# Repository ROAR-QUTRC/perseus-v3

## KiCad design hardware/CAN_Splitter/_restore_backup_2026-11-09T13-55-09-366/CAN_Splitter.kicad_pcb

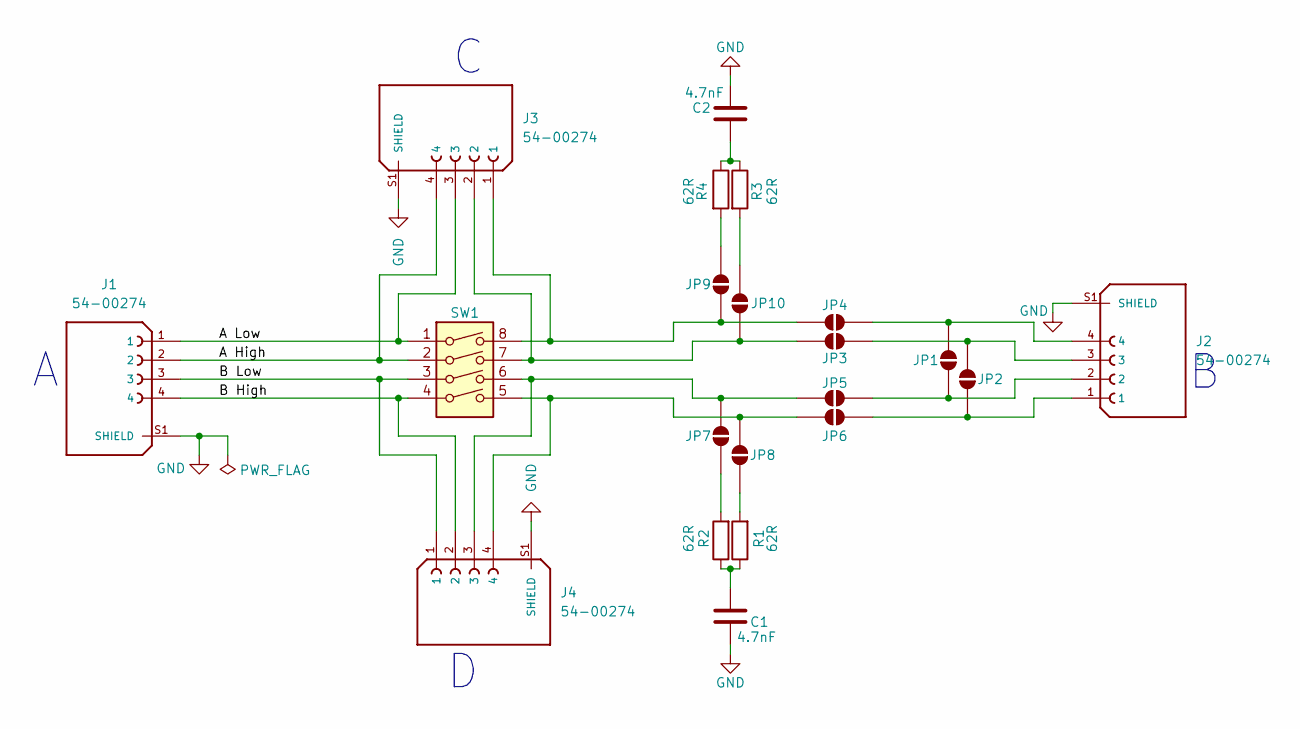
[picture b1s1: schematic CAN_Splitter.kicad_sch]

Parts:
C1, C2: 4.7nF; C_0603_1608Metric; digikey_part_num 1276-CL03B472KASVPNCCT-ND
J1, J2, J3, J4: 54-00274; TENSILITY_54-00274; MPN 54-00274; DigiKey_Part_Number 839-54-00274-ND
JP1, JP2, JP3, JP4, JP5, JP6, JP7, JP8, JP9, JP10: SolderJumper_2_Open; SolderJumper-2_P1.3mm_Open_RoundedPad1.0x1.5mm
R1, R2, R3, R4: 62R; C_0603_1608Metric; digikey_part_num RMCF0603FT62R0CT-ND
SW1: SW_DIP_x04; SW_DIP_SPSTx04_Slide_Copal_CHS-04A_W5.08mm_P1.27mm_JPin

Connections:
/A High: J1.2, J3.4, SW1.2
/A Low: J1.1, J3.3, SW1.1
/B High: J1.4, J4.2, SW1.4
/B Low: J1.3, J4.1, SW1.3
GND: C1.2, C2.2, J1.S1 (SHIELD), J1.S2 (SHIELD), J2.S1 (SHIELD), J2.S2 (SHIELD), J3.S1 (SHIELD), J3.S2 (SHIELD), J4.S1 (SHIELD), J4.S2 (SHIELD)
unnamed: C1.1, R1.1, R2.1
unnamed: C2.1, R3.1, R4.1
unnamed: J2.2, JP1.1 (A), JP5.1 (A)
unnamed: J2.4, JP1.2 (B), JP4.1 (A)
unnamed: J2.1, JP2.1 (A), JP6.1 (A)
unnamed: J2.3, JP2.2 (B), JP3.1 (A)
unnamed: J3.1, JP4.2 (B), JP9.2 (B), SW1.8
unnamed: J4.3, JP5.2 (B), JP7.2 (B), SW1.6
unnamed: J4.4, JP6.2 (B), JP8.2 (B), SW1.5
unnamed: JP7.1 (A), R2.2
unnamed: JP8.1 (A), R1.2
unnamed: JP9.1 (A), R4.2
unnamed: JP10.1 (A), R3.2
unnamed: J3.2, JP3.2 (B), JP10.2 (B), SW1.7

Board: 2 copper layers, 21 parts (0 on the bottom side), 19 nets, no tracks yet.

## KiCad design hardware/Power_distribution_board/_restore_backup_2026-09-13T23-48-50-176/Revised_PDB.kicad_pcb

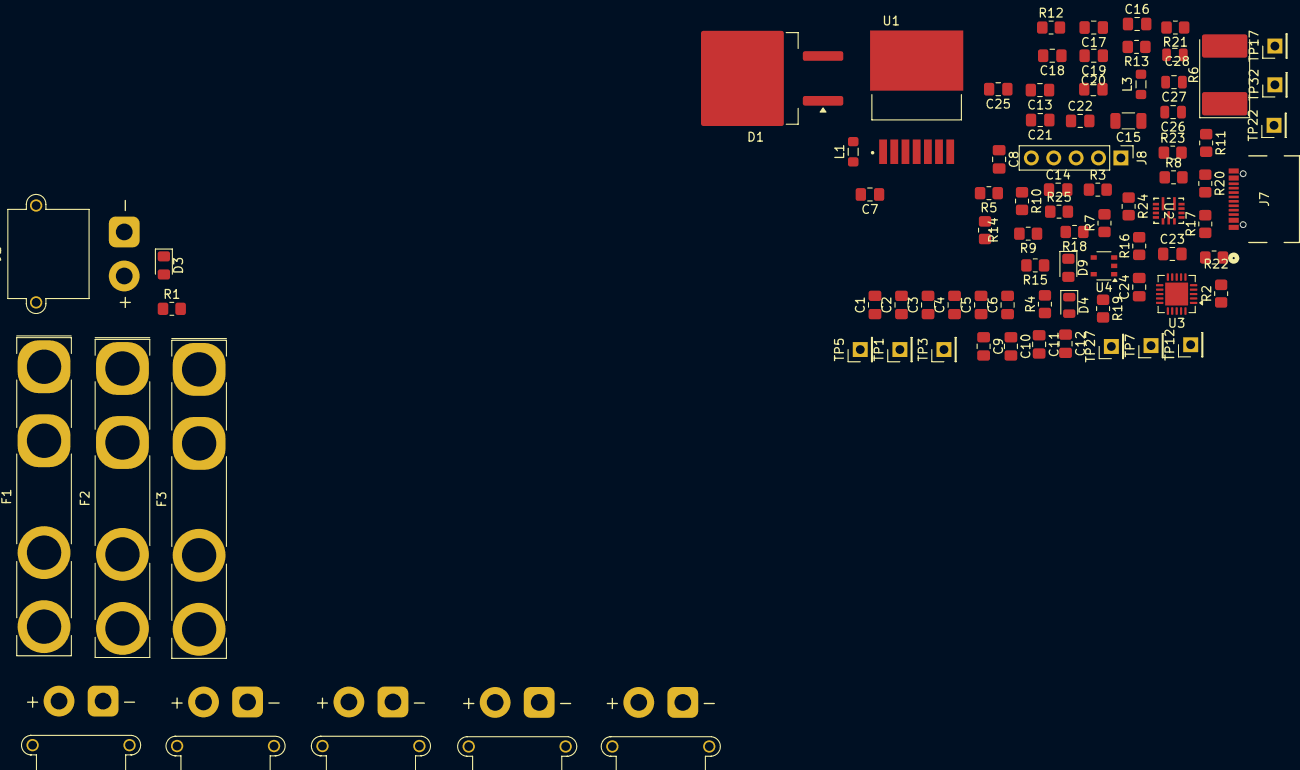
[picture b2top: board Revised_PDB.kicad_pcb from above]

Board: 4 copper layers, 83 parts (0 on the bottom side), 43 nets, no tracks yet.

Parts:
C1, C2, C3: 15u; C_0805_2012Metric_Pad1.18x1.45mm_HandSolder
C4: 0.47u; C_0805_2012Metric_Pad1.18x1.45mm_HandSolder
C5, C6: 180u; C_0805_2012Metric_Pad1.18x1.45mm_HandSolder
C7: 0.01u; C_0805_2012Metric_Pad1.18x1.45mm_HandSolder
C8: 100u; C_0805_2012Metric_Pad1.18x1.45mm_HandSolder
C9, C10, C11, C17, C18, C19: 10u; C_0805_2012Metric_Pad1.18x1.45mm_HandSolder
C12: 100n; C_0805_2012Metric_Pad1.18x1.45mm_HandSolder
C13, C21, C22: 2.2u; C_0805_2012Metric_Pad1.18x1.45mm_HandSolder
C14: 1nF; C_0805_2012Metric_Pad1.18x1.45mm_HandSolder
C15: 1u; C_1206_3216Metric
C16: 22pF; C_0805_2012Metric_Pad1.18x1.45mm_HandSolder
C20: 47u; C_0805_2012Metric_Pad1.18x1.45mm_HandSolder
C23: 470n; C_0805_2012Metric_Pad1.18x1.45mm_HandSolder
C24, C25: 390p; C_0805_2012Metric_Pad1.18x1.45mm_HandSolder
C26, C27: 1n; C_0805_2012Metric
C28: 10n; C_0805_2012Metric
D1: 6TQ035S; TO-263-2
D3, D9: LED; LED_0805_2012Metric_Pad1.15x1.40mm_HandSolder
D4: LED; LED_0805_2012Metric
F1, F2: 5A; Fuseholder_Keystone_3555-2
F3: 20A; Fuseholder_Keystone_3555-2
J1: xt30_PWR_IN; AMASS_XT30PW-M_1x02_P2.50mm_Horizontal
J2, J3, J4, J5, J6: XT30_VOUT1; AMASS_XT30PW-F_1x02_P2.50mm_Horizontal
J7: USB_C_Receptacle_USB2.0_16P; USB4105_GCT
J8: Conn_01x05; PinHeader_1x05_P2.54mm_Vertical
L1: L; L_0805_2012Metric_Pad1.05x1.20mm_HandSolder
L3: 4.7u; L_0805_2012Metric_Pad1.05x1.20mm_HandSolder
R1, R18: R; R_0805_2012Metric_Pad1.20x1.40mm_HandSolder
R2, R3: 10k; R_0805_2012Metric_Pad1.20x1.40mm_HandSolder
R4, R5: 2.2k; R_0805_2012Metric_Pad1.20x1.40mm_HandSolder
R6: 300k; D_3220_8050Metric_Pad2.65x5.15mm_HandSolder
R7: 6.8k; R_0805_2012Metric_Pad1.20x1.40mm_HandSolder
R8: 51k; R_0805_2012Metric_Pad1.20x1.40mm_HandSolder
R9, R11, R16, R17: 0; R_0805_2012Metric_Pad1.20x1.40mm_HandSolder
R10, R14, R15, R22, R23, R24, R25: DNF; R_0805_2012Metric_Pad1.20x1.40mm_HandSolder
R12: 100k; R_0805_2012Metric_Pad1.20x1.40mm_HandSolder
R13: 11k; R_0805_2012Metric_Pad1.20x1.40mm_HandSolder
R19, R20: 2.2; R_0805_2012Metric_Pad1.20x1.40mm_HandSolder
R21: 1M; R_0805_2012Metric_Pad1.20x1.40mm_HandSolder
TP1: Feeback; PinHeader_1x01_P2.54mm_Vertical
TP3: VOUT; PinHeader_1x01_P2.54mm_Vertical
TP5: VIN; PinHeader_1x01_P2.54mm_Vertical
TP7: VBUS; PinHeader_1x01_P2.54mm_Vertical
TP12: VDRV; PinHeader_1x01_P2.54mm_Vertical
TP17: DM; PinHeader_1x01_P2.54mm_Vertical
TP22: DP; PinHeader_1x01_P2.54mm_Vertical
TP27: CC1; PinHeader_1x01_P2.54mm_Vertical
TP32: CC2; PinHeader_1x01_P2.54mm_Vertical
U1: LM2678SX-12_NOPB; TO127P1435X464-8N
U2: MP2491CGQB-Z; QFN-13_2p5MMx3MM_MNP
U3: MP5031GRE-00A3-P; QFN-20-1EP_4x4mm_P0.5mm_EP2.6x2.6mm
U4: TPD4E1U06DBVR; TSOP-5_1.65x3.05mm_P0.95mm

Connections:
+5V: C13.2, C21.2, J8.5, R2.1, R3.1, R5.1, R10.1, R14.1, R22.1, R23.1, R24.1, R25.1, U2.3 (VCC), U3.7 (VCC)
/12 Volt Reg/VIN: C1.1, C2.1, C3.1, C4.1, F3.2, J2.2, J3.2, J4.2, R1.2, TP5.1 (1_1), U1.2 (INPUT)
/12 Volt Reg/VOUT: C5.1, C6.1, F1.1, L1.2, TP1.1 (1_1), TP3.1 (1_1), U1.6 (FB)
/USB_pd/GPIO2: R22.2, U3.11 (GPIO2)
/USB_pd/GPIO3: R23.2, U3.9 (GPIO3)
/USB_pd/GPIO4: R24.2, U3.10 (GPIO4)
/USB_pd/GPIO5: R25.2, U3.4 (GPIO5)
/USB_pd/PG: R4.2, R5.2, U2.13 (PG)
/USB_pd/SCL: J8.2, U3.2 (SCL)
/USB_pd/SDA: J8.3, U3.1 (SDA)
/USB_pd/VIN: C8.2, C9.1, C10.1, C11.1, C12.1, R6.2, U2.1 (IN)
/USB_pd/VSEL1: R3.2, R17.2, U2.4 (VSEL1)
/USB_pd/VSEL2: R2.2, R16.2, U2.5 (VSEL2)
GND: C1.2, C2.2, C3.2, C4.2, C5.2, C6.2, C8.1, C9.2, C10.2, C11.2, C12.2, C13.1, C14.1, C17.2, C18.2, C19.2, C20.2, C21.1, C22.1, C23.1, C24.1, C25.1, C26.2, C27.2, C28.2, D1.3 (A), D3.1 (K), D4.1 (K), D9.1 (K), J1.1, J2.1, J3.1, J4.1, J5.1, J6.1, J8.1, R8.1, R9.1, R13.2, R15.2, R18.2, R21.1, U1.4 (GND), U2.2 (PGND), U2.7 (AGND), U4.2
unnamed: C15.2, R11.1
unnamed: C7.2, D1.2 (K), L1.1, U1.1 (SWITCH_OUTPUT)
unnamed: D3.2 (A), R1.1
unnamed: D4.2 (A), R4.1
unnamed: D9.2 (A), R7.1
unnamed: F3.1, J1.2
unnamed: F1.2, J5.2
unnamed: F2.2, J6.2
unnamed: J7.A5 (CC1), R19.1, TP27.1 (1_1), U4.3
unnamed: J7.B5 (CC2), R20.1, TP32.1 (1_1), U4.4
unnamed: C28.1, R21.2
unnamed: J8.4, R18.1, U3.5 (I2C_MODE)
unnamed: C7.1, U1.3 (CB)
unnamed: R11.2, U2.9 (BST)
unnamed: C14.2, R6.1, R7.2, U2.11 (EN)
unnamed: C16.2, R12.2, R13.1, U2.6 (FB)
unnamed: R8.2, U2.12 (ILIM)
unnamed: R9.2, R10.2, U2.10 (MODE)
unnamed: C15.1, L3.1, U2.8 (SW)
unnamed: C24.2, R19.2, U3.15 (CC1)
unnamed: C25.2, R20.2, U3.14 (CC2)
unnamed: C26.1, J7.A7 (D-), J7.B7 (D-), TP17.1 (1_1), U3.17 (DM)
unnamed: C27.1, J7.A6 (D+), J7.B6 (D+), TP22.1 (1_1), U3.16 (DP), U4.1
unnamed: R17.1, U3.3 (GPIO1)
unnamed: R16.1, U3.12 (GPIO6)
unnamed: R14.2, R15.1, U3.13 (NTC)
unnamed: C23.2, U3.6 (VDD)
unnamed: TP12.1 (1_1), U3.19 (VDRV)
VBUS: C16.1, C17.1, C18.1, C19.1, C20.1, C22.2, L3.2, R12.1, TP7.1 (1_1), U3.20 (VBUS_P)
